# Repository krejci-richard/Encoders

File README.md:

# Encoders
LPD3806 optical encoder
It is a cheap optical encoder from China. They suffer from many compromises that degrade serious results.

- supply voltage is recommended 5-24V - it is wrong. Encoder contains a classic linear stabilizer 7805, which needs for its proper operation at least 7.5V. When powering 5V encoder works poorly (electronics gets instead of 5V only about 2.5V), losing pulses.
- with 12-24V power supply there is another problem with heat dissipation at 7805

- Another problem is the transmission of the quadrature signal. The encoder is connected as an open collector. Although the cable is shielded, but if it leads around the induction power supply (switched power supplies, stepper motor, ...) the signal is very susceptible to interference.

After reworking:
- output reworked to DIFFERENTIAL LINE DRIVER
- supply voltage is only 5V, no protection !!!
- added non-inverting Schmitt trigger

To rework your encoder, you will need to carefully disassemble it and most components will be reused.

Tools:
- screwdriver
- table solder
- heat gun
- tweezers
- good luck

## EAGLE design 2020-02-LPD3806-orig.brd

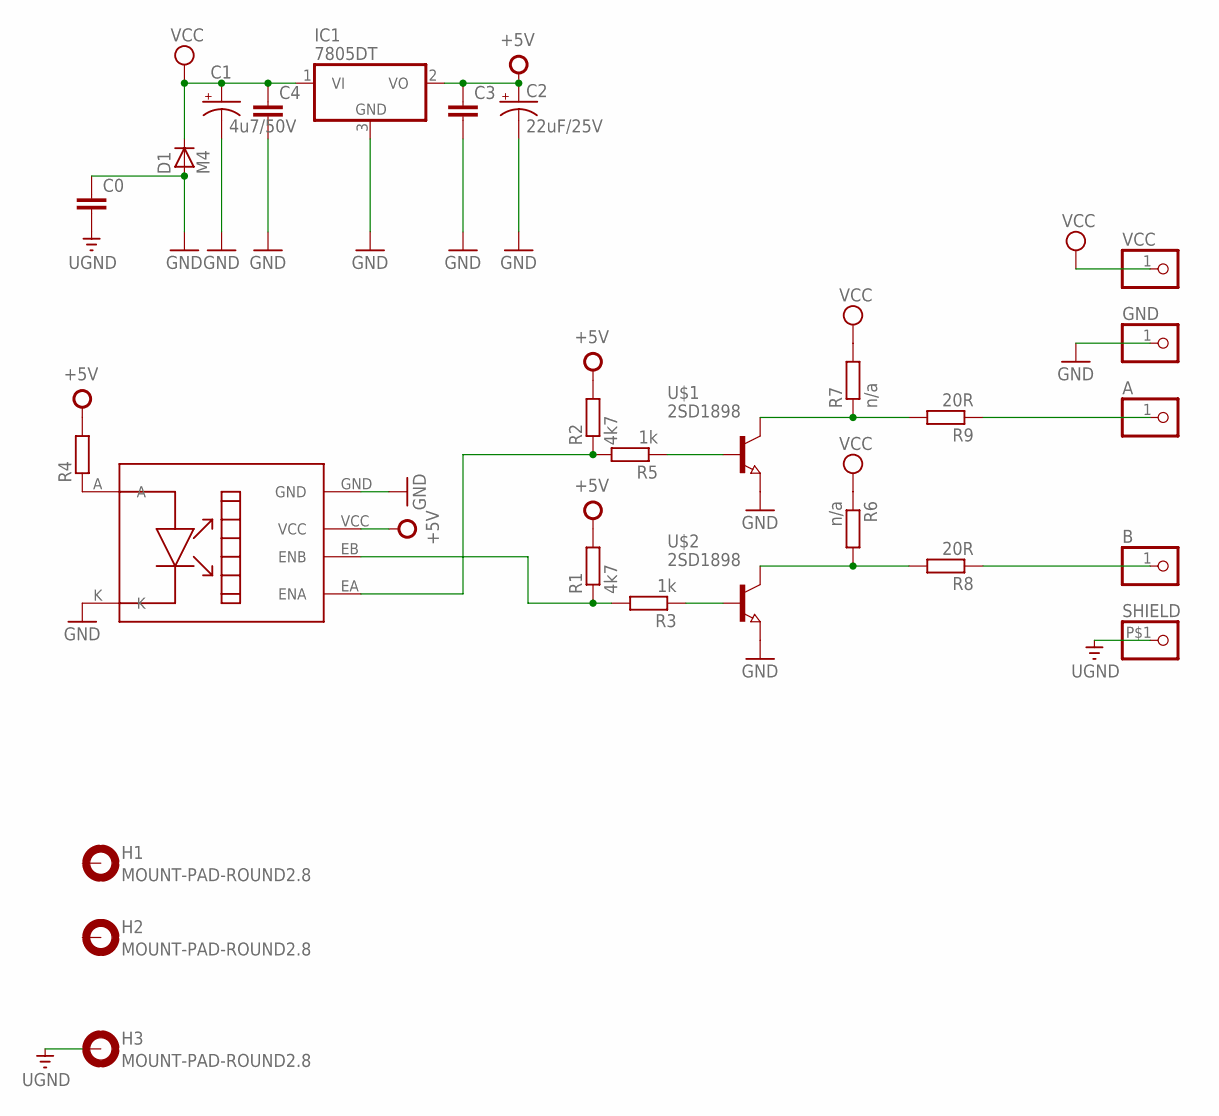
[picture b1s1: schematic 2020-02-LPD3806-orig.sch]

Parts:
A: PINHD-1X1; 1X01
B: PINHD-1X1; 1X01
C0: C-EUC1206; C1206
C1: 4u7/50V; 153CLV-0405
C2: 22uF/25V; 153CLV-0505
C3, C4: C-EUC0805; C0805
D1: M4; SOD-123
GND: PINHD-1X1; 1X01
H1, H2, H3: MOUNT-PAD-ROUND2.8; 2,8-PAD
IC1: 7805DT; TO252
R1, R2: 4k7; R0805
R3, R5: 1k; R0805
R4: R-EU_R1206; R1206
R6, R7: n/a; R1206
R8, R9: 20R; R1206
SHIELD: PINHD-1X1-BIGPOGO; 1X1-BIGPOGO
U$1, U$2: 2SD1898; SOT-89
U$3: N30-6841
VCC: PINHD-1X1; 1X01

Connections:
+5V: C2.+, C3.1, IC1.2 (VO), R1.2, R2.2, R4.2, U$3.VCC
GND: C0.1, C1.-, C2.-, C3.2, C4.2, D1.A, GND.1, IC1.3 (GND), U$1.E, U$2.E, U$3.GND, U$3.K
unnamed: A.1, R9.1
unnamed: R7.1, R9.2, U$1.C1 (C), U$1.C2 (C)
unnamed: B.1, R8.1
unnamed: R6.2, R8.2, U$2.C1 (C), U$2.C2 (C)
unnamed: R4.1, U$3.A
unnamed: R2.1, R5.2, U$3.EA (ENA)
unnamed: R5.1, U$1.B
unnamed: R1.1, R3.2, U$3.EB (ENB)
unnamed: R3.1, U$2.B
UGND: C0.2, H3.B2,8, SHIELD.P$1
VCC: C1.+, C4.1, D1.C, IC1.1 (VI), R6.1, R7.2, VCC.1

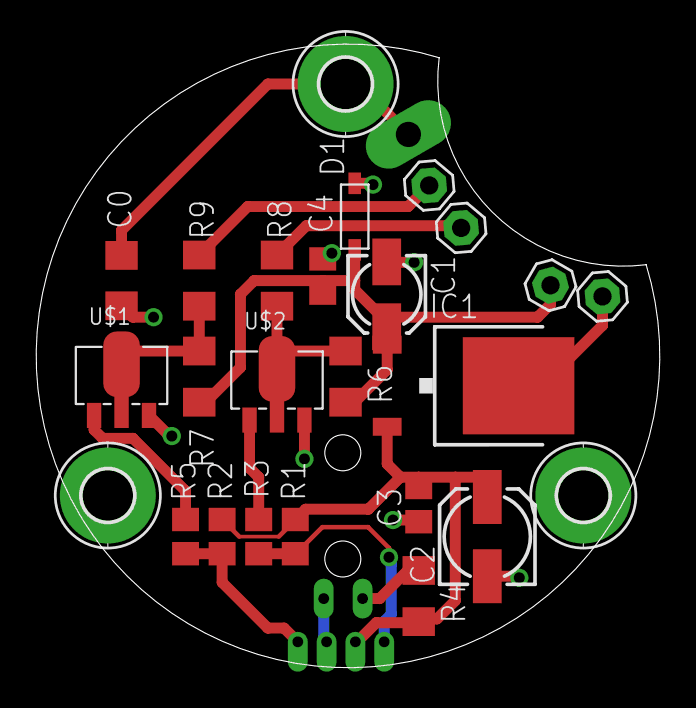
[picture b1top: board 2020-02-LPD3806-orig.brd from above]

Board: 2 copper layers, 34.6 x 34.6 mm, 27 parts (0 on the bottom side), 13 nets.

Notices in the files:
parts and their libraries:
supply0: Copyright (C) 2007, Bob Starr
